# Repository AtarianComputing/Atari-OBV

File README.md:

# Atari-OBV
Project to create OpenBoardView files for the Atari line of computers to aid repair and restoration.

## OpenBoardView
Excellent open source board view software.
http://openboardview.org

## KiCad to BoardView Exporter
Python plugin to convert PCB file to OBV BRD.
https://github.com/whitequark/kicad-boardview

## Issues
My resulting BRD is mirrored and upside down for some reason. Haven't figured out how to fix it. But rotation and mirroring is quick and easy to do in software

Active low signals. KiCad needs to have the Pin/Net name enclosed in the tilde ~ character for it to display properly in KiCad. Those nets appear as ~BR~ in OBV. Easy enough to RegEx into /BR.

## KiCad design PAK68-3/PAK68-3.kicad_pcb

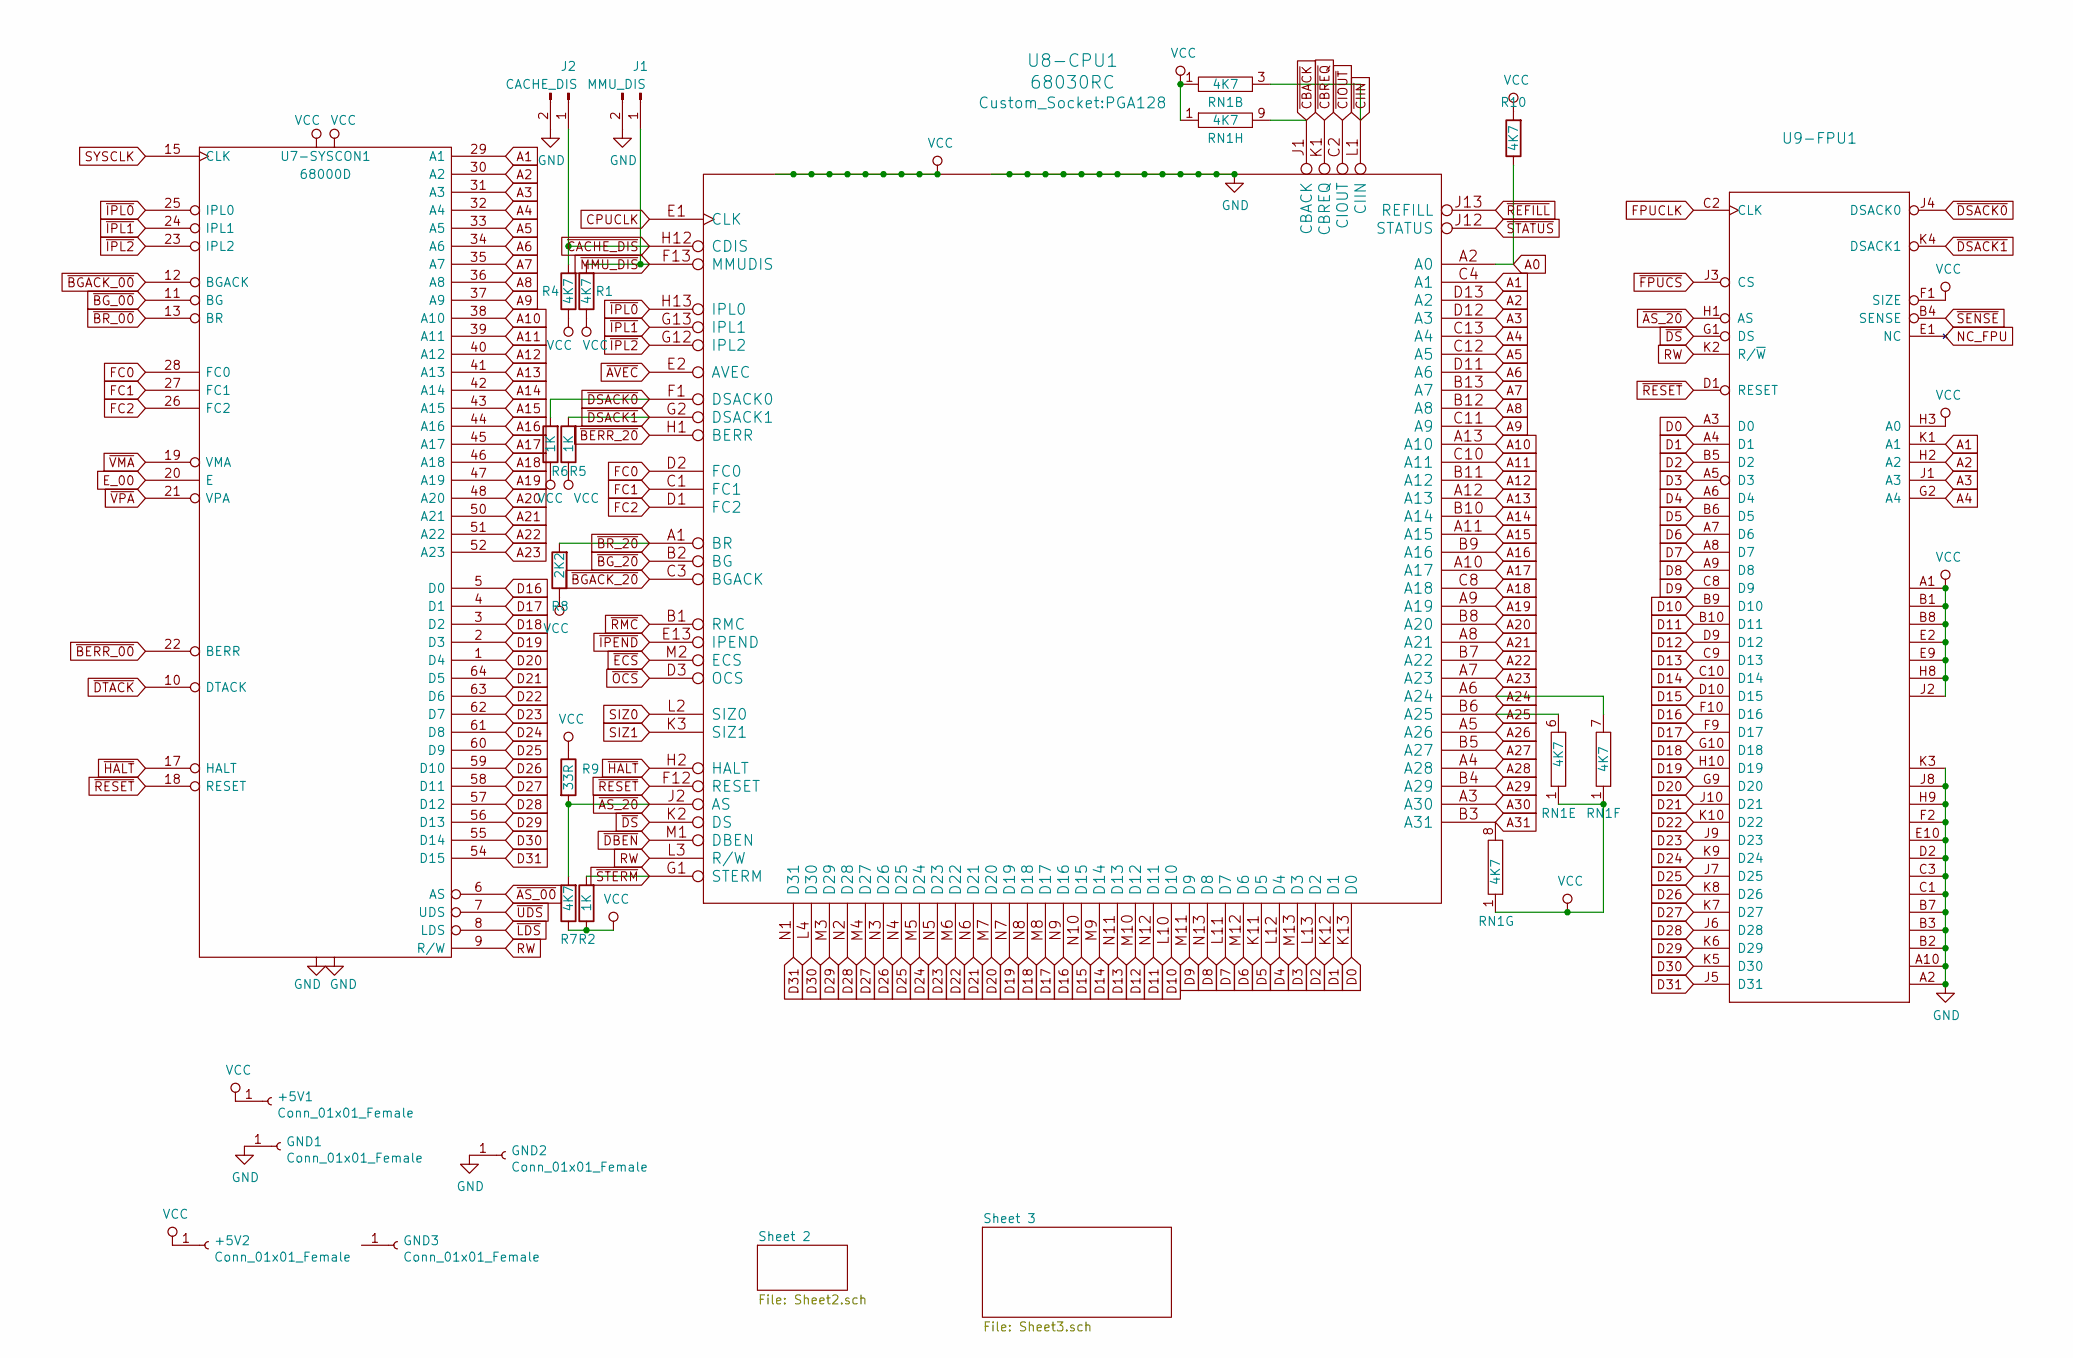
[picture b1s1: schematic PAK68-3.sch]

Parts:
+5V1, +5V2: Conn_01x01_Female; MountingHole_2.2mm_M2_DIN965_Pad
GND1, GND2, GND3: Conn_01x01_Female; MountingHole_2.2mm_M2_DIN965_Pad
J1: MMU_DIS; Socket_Strip_Straight_1x02_Pitch2.54mm
J2: CACHE_DIS; Socket_Strip_Straight_1x02_Pitch2.54mm
R1, R4, R7, R10: 4K7; R_Axial_DIN0207_L6.3mm_D2.5mm_P10.16mm_Horizontal
R2, R5, R6: 1K; R_Axial_DIN0207_L6.3mm_D2.5mm_P10.16mm_Horizontal
R8: 2K2; R_Axial_DIN0207_L6.3mm_D2.5mm_P10.16mm_Horizontal
R9: 33R; R_Axial_DIN0207_L6.3mm_D2.5mm_P10.16mm_Horizontal
RN1: 4K7; R_Array_SIP9
U7-SYSCON1: 68000D; DIP-64_W22.86mm_Socket
U8-CPU1: 68030RC; PGA128
U9-FPU1: MC68882; PGA68

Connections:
A0: R10.1, U8-CPU1.A2 (A0); also elsewhere on the board
A1: U7-SYSCON1.29 (A1), U8-CPU1.C4 (A1), U9-FPU1.K1 (A1); also elsewhere on the board
A2: U7-SYSCON1.30 (A2), U8-CPU1.D13 (A2), U9-FPU1.H2 (A2); also elsewhere on the board
A3: U7-SYSCON1.31 (A3), U8-CPU1.D12 (A3), U9-FPU1.J1 (A3); also elsewhere on the board
A4: U7-SYSCON1.32 (A4), U8-CPU1.C13 (A4), U9-FPU1.G2 (A4); also elsewhere on the board
A5: U7-SYSCON1.33 (A5), U8-CPU1.C12 (A5); also elsewhere on the board
A6: U7-SYSCON1.34 (A6), U8-CPU1.D11 (A6); also elsewhere on the board
A7: U7-SYSCON1.35 (A7), U8-CPU1.B13 (A7); also elsewhere on the board
A8: U7-SYSCON1.36 (A8), U8-CPU1.B12 (A8); also elsewhere on the board
A9: U7-SYSCON1.37 (A9), U8-CPU1.C11 (A9); also elsewhere on the board
A10: U7-SYSCON1.38 (A10), U8-CPU1.A13 (A10); also elsewhere on the board
A11: U7-SYSCON1.39 (A11), U8-CPU1.C10 (A11); also elsewhere on the board
A12: U7-SYSCON1.40 (A12), U8-CPU1.B11 (A12); also elsewhere on the board
A13: U7-SYSCON1.41 (A13), U8-CPU1.A12 (A13); also elsewhere on the board
A14: U7-SYSCON1.42 (A14), U8-CPU1.B10 (A14); also elsewhere on the board
A15: U7-SYSCON1.43 (A15), U8-CPU1.A11 (A15); also elsewhere on the board
A16: U7-SYSCON1.44 (A16), U8-CPU1.B9 (A16); also elsewhere on the board
A17: U7-SYSCON1.45 (A17), U8-CPU1.A10 (A17); also elsewhere on the board
A18: U7-SYSCON1.46 (A18), U8-CPU1.C8 (A18); also elsewhere on the board
A19: U7-SYSCON1.47 (A19), U8-CPU1.A9 (A19); also elsewhere on the board
A20: U7-SYSCON1.48 (A20), U8-CPU1.B8 (A20); also elsewhere on the board
A21: U7-SYSCON1.50 (A21), U8-CPU1.A8 (A21); also elsewhere on the board
A22: U7-SYSCON1.51 (A22), U8-CPU1.B7 (A22); also elsewhere on the board
A23: U7-SYSCON1.52 (A23), U8-CPU1.A7 (A23); also elsewhere on the board
A24: RN1.7, U8-CPU1.A6 (A24); also elsewhere on the board
A25: RN1.6, U8-CPU1.B6 (A25); also elsewhere on the board
A26: U8-CPU1.A5 (A26)
A27: U8-CPU1.B5 (A27)
A28: U8-CPU1.A4 (A28)
A29: U8-CPU1.B4 (A29)
A30: U8-CPU1.A3 (A30)
A31: RN1.8, U8-CPU1.B3 (A31); also elsewhere on the board
CPUCLK: U8-CPU1.E1 (CLK); also elsewhere on the board
D0: U8-CPU1.K13 (D0), U9-FPU1.A3 (D0); also elsewhere on the board
D1: U8-CPU1.K12 (D1), U9-FPU1.A4 (D1); also elsewhere on the board
D2: U8-CPU1.L13 (D2), U9-FPU1.B5 (D2); also elsewhere on the board
D3: U8-CPU1.M13 (D3), U9-FPU1.A5 (D3); also elsewhere on the board
D4: U8-CPU1.L12 (D4), U9-FPU1.A6 (D4); also elsewhere on the board
D5: U8-CPU1.K11 (D5), U9-FPU1.B6 (D5); also elsewhere on the board
D6: U8-CPU1.M12 (D6), U9-FPU1.A7 (D6); also elsewhere on the board
D7: U8-CPU1.L11 (D7), U9-FPU1.A8 (D7); also elsewhere on the board
D8: U8-CPU1.N13 (D8), U9-FPU1.A9 (D8); also elsewhere on the board
D9: U8-CPU1.M11 (D9), U9-FPU1.C8 (D9); also elsewhere on the board
D10: U8-CPU1.L10 (D10), U9-FPU1.B9 (D10); also elsewhere on the board
D11: U8-CPU1.N12 (D11), U9-FPU1.B10 (D11); also elsewhere on the board
D12: U8-CPU1.M10 (D12), U9-FPU1.D9 (D12); also elsewhere on the board
D13: U8-CPU1.N11 (D13), U9-FPU1.C9 (D13); also elsewhere on the board
D14: U8-CPU1.M9 (D14), U9-FPU1.C10 (D14); also elsewhere on the board
D15: U8-CPU1.N10 (D15), U9-FPU1.D10 (D15); also elsewhere on the board
D16: U7-SYSCON1.5 (D0), U8-CPU1.N9 (D16), U9-FPU1.F10 (D16); also elsewhere on the board
D17: U7-SYSCON1.4 (D1), U8-CPU1.M8 (D17), U9-FPU1.F9 (D17); also elsewhere on the board
D18: U7-SYSCON1.3 (D2), U8-CPU1.N8 (D18), U9-FPU1.G10 (D18); also elsewhere on the board
D19: U7-SYSCON1.2 (D3), U8-CPU1.N7 (D19), U9-FPU1.H10 (D19); also elsewhere on the board
D20: U7-SYSCON1.1 (D4), U8-CPU1.M7 (D20), U9-FPU1.G9 (D20); also elsewhere on the board
D21: U7-SYSCON1.64 (D5), U8-CPU1.N6 (D21), U9-FPU1.J10 (D21); also elsewhere on the board
D22: U7-SYSCON1.63 (D6), U8-CPU1.M6 (D22), U9-FPU1.K10 (D22); also elsewhere on the board
D23: U7-SYSCON1.62 (D7), U8-CPU1.N5 (D23), U9-FPU1.J9 (D23); also elsewhere on the board
D24: U7-SYSCON1.61 (D8), U8-CPU1.M5 (D24), U9-FPU1.K9 (D24); also elsewhere on the board
D25: U7-SYSCON1.60 (D9), U8-CPU1.N4 (D25), U9-FPU1.J7 (D25); also elsewhere on the board
D26: U7-SYSCON1.59 (D10), U8-CPU1.N3 (D26), U9-FPU1.K8 (D26); also elsewhere on the board
D27: U7-SYSCON1.58 (D11), U8-CPU1.M4 (D27), U9-FPU1.K7 (D27); also elsewhere on the board
D28: U7-SYSCON1.57 (D12), U8-CPU1.N2 (D28), U9-FPU1.J6 (D28); also elsewhere on the board
D29: U7-SYSCON1.56 (D13), U8-CPU1.M3 (D29), U9-FPU1.K6 (D29); also elsewhere on the board
D30: U7-SYSCON1.55 (D14), U8-CPU1.L4 (D30), U9-FPU1.K5 (D30); also elsewhere on the board
D31: U7-SYSCON1.54 (D15), U8-CPU1.N1 (D31), U9-FPU1.J5 (D31); also elsewhere on the board
E_00: U7-SYSCON1.20 (E); also elsewhere on the board
FC0: U7-SYSCON1.28 (FC0), U8-CPU1.D2 (FC0); also elsewhere on the board
FC1: U7-SYSCON1.27 (FC1), U8-CPU1.C1 (FC1); also elsewhere on the board
FC2: U7-SYSCON1.26 (FC2), U8-CPU1.D1 (FC2); also elsewhere on the board
FPUCLK: U9-FPU1.C2 (CLK); also elsewhere on the board
GND: GND1.1, GND2.1, J1.2, J2.2, U7-SYSCON1.16 (GND), U7-SYSCON1.53 (GND), U8-CPU1.C5 (GND), U8-CPU1.C7 (GND), U8-CPU1.C9 (GND), U8-CPU1.E3 (GND), U8-CPU1.E11 (GND), U8-CPU1.F3 (GND), U8-CPU1.G3 (GND), U8-CPU1.G11 (GND), U8-CPU1.J3 (GND), U8-CPU1.J11 (GND), U8-CPU1.L5 (GND), U8-CPU1.L7 (GND), U8-CPU1.L8 (GND), U8-CPU1.L9 (GND), U9-FPU1.A2 (GND@1), U9-FPU1.A10 (GND@2), U9-FPU1.B2 (GND@3), U9-FPU1.B3 (GND@4), U9-FPU1.B7 (GND@5), U9-FPU1.C1 (GND@6), U9-FPU1.C3 (GND@7), U9-FPU1.D2 (GND@8), U9-FPU1.E10 (GND@9), U9-FPU1.F2 (GND@10), U9-FPU1.H9 (GND@11), U9-FPU1.J8 (GND@12), U9-FPU1.K3 (GND@13); also elsewhere on the board
NC_FPU: U9-FPU1.E1 (NC)
RW: U7-SYSCON1.9 (R/W), U8-CPU1.L3 (R/W), U9-FPU1.K2 (R/~W); also elsewhere on the board
SIZ0: U8-CPU1.L2 (SIZ0); also elsewhere on the board
SIZ1: U8-CPU1.K3 (SIZ1); also elsewhere on the board
SYSCLK: U7-SYSCON1.15 (CLK); also elsewhere on the board
VCC: +5V1.1, +5V2.1, R1.1, R2.1, R4.1, R5.1, R6.1, R7.1, R8.1, R9.1, R10.2, RN1.1, U7-SYSCON1.14 (VCC), U7-SYSCON1.49 (VCC), U8-CPU1.C6 (VCC), U8-CPU1.D4 (VCC), U8-CPU1.D10 (VCC), U8-CPU1.F2 (VCC), U8-CPU1.F11 (VCC), U8-CPU1.H3 (VCC), U8-CPU1.H11 (VCC), U8-CPU1.K4 (VCC), U8-CPU1.K10 (VCC), U8-CPU1.L6 (VCC), U9-FPU1.A1 (VCC@1), U9-FPU1.B1 (VCC@2), U9-FPU1.B8 (VCC@3), U9-FPU1.E2 (VCC@4), U9-FPU1.E9 (VCC@5), U9-FPU1.F1 (SIZE), U9-FPU1.H3 (A0), U9-FPU1.H8 (VCC@6), U9-FPU1.J2 (VCC@7); also elsewhere on the board
~AS_00~: U7-SYSCON1.6 (AS); also elsewhere on the board
~AS_20~: R7.2, R9.2, U8-CPU1.J2 (AS), U9-FPU1.H1 (AS); also elsewhere on the board
~AVEC~: U8-CPU1.E2 (AVEC); also elsewhere on the board
~BERR_00~: U7-SYSCON1.22 (BERR); also elsewhere on the board
~BERR_20~: U8-CPU1.H1 (BERR); also elsewhere on the board
~BGACK_00~: U7-SYSCON1.12 (BGACK); also elsewhere on the board
~BGACK_20~: U8-CPU1.C3 (BGACK); also elsewhere on the board
~BG_00~: U7-SYSCON1.11 (BG); also elsewhere on the board
~BG_20~: U8-CPU1.B2 (BG); also elsewhere on the board
~BR_00~: U7-SYSCON1.13 (BR); also elsewhere on the board
~BR_20~: R8.2, U8-CPU1.A1 (BR); also elsewhere on the board
~CACHE_DIS~: J2.1, R4.2, U8-CPU1.H12 (CDIS)
~CBACK~: RN1.9, U8-CPU1.J1 (CBACK)
~CBREQ~: U8-CPU1.K1 (CBREQ)
~CIIN~: RN1.3, U8-CPU1.L1 (CIIN)
~CIOUT~: U8-CPU1.C2 (CIOUT)
~DBEN~: U8-CPU1.M1 (DBEN)
~DSACK0~: R6.2, U8-CPU1.F1 (DSACK0), U9-FPU1.J4 (DSACK0); also elsewhere on the board
~DSACK1~: R5.2, U8-CPU1.G2 (DSACK1), U9-FPU1.K4 (DSACK1); also elsewhere on the board
~DS~: U8-CPU1.K2 (DS), U9-FPU1.G1 (DS); also elsewhere on the board
~DTACK~: U7-SYSCON1.10 (DTACK); also elsewhere on the board
~ECS~: U8-CPU1.M2 (ECS)
~FPUCS~: U9-FPU1.J3 (CS); also elsewhere on the board
~HALT~: U7-SYSCON1.17 (HALT), U8-CPU1.H2 (HALT); also elsewhere on the board
~IPEND~: U8-CPU1.E13 (IPEND)
~IPL0~: U7-SYSCON1.25 (IPL0), U8-CPU1.H13 (IPL0); also elsewhere on the board
~IPL1~: U7-SYSCON1.24 (IPL1), U8-CPU1.G13 (IPL1); also elsewhere on the board
~IPL2~: U7-SYSCON1.23 (IPL2), U8-CPU1.G12 (IPL2); also elsewhere on the board
~LDS~: U7-SYSCON1.8 (LDS); also elsewhere on the board
~MMU_DIS~: J1.1, R1.2, U8-CPU1.F13 (MMUDIS)
~OCS~: U8-CPU1.D3 (OCS)
~REFILL~: U8-CPU1.J13 (REFILL)
~RESET~: U7-SYSCON1.18 (RESET), U8-CPU1.F12 (RESET), U9-FPU1.D1 (RESET); also elsewhere on the board
~RMC~: U8-CPU1.B1 (RMC)
~SENSE~: U9-FPU1.B4 (SENSE)
~STATUS~: U8-CPU1.J12 (STATUS)
~STERM~: R2.2, U8-CPU1.G1 (STERM)
~UDS~: U7-SYSCON1.7 (UDS); also elsewhere on the board
~VMA~: U7-SYSCON1.19 (VMA); also elsewhere on the board
~VPA~: U7-SYSCON1.21 (VPA); also elsewhere on the board

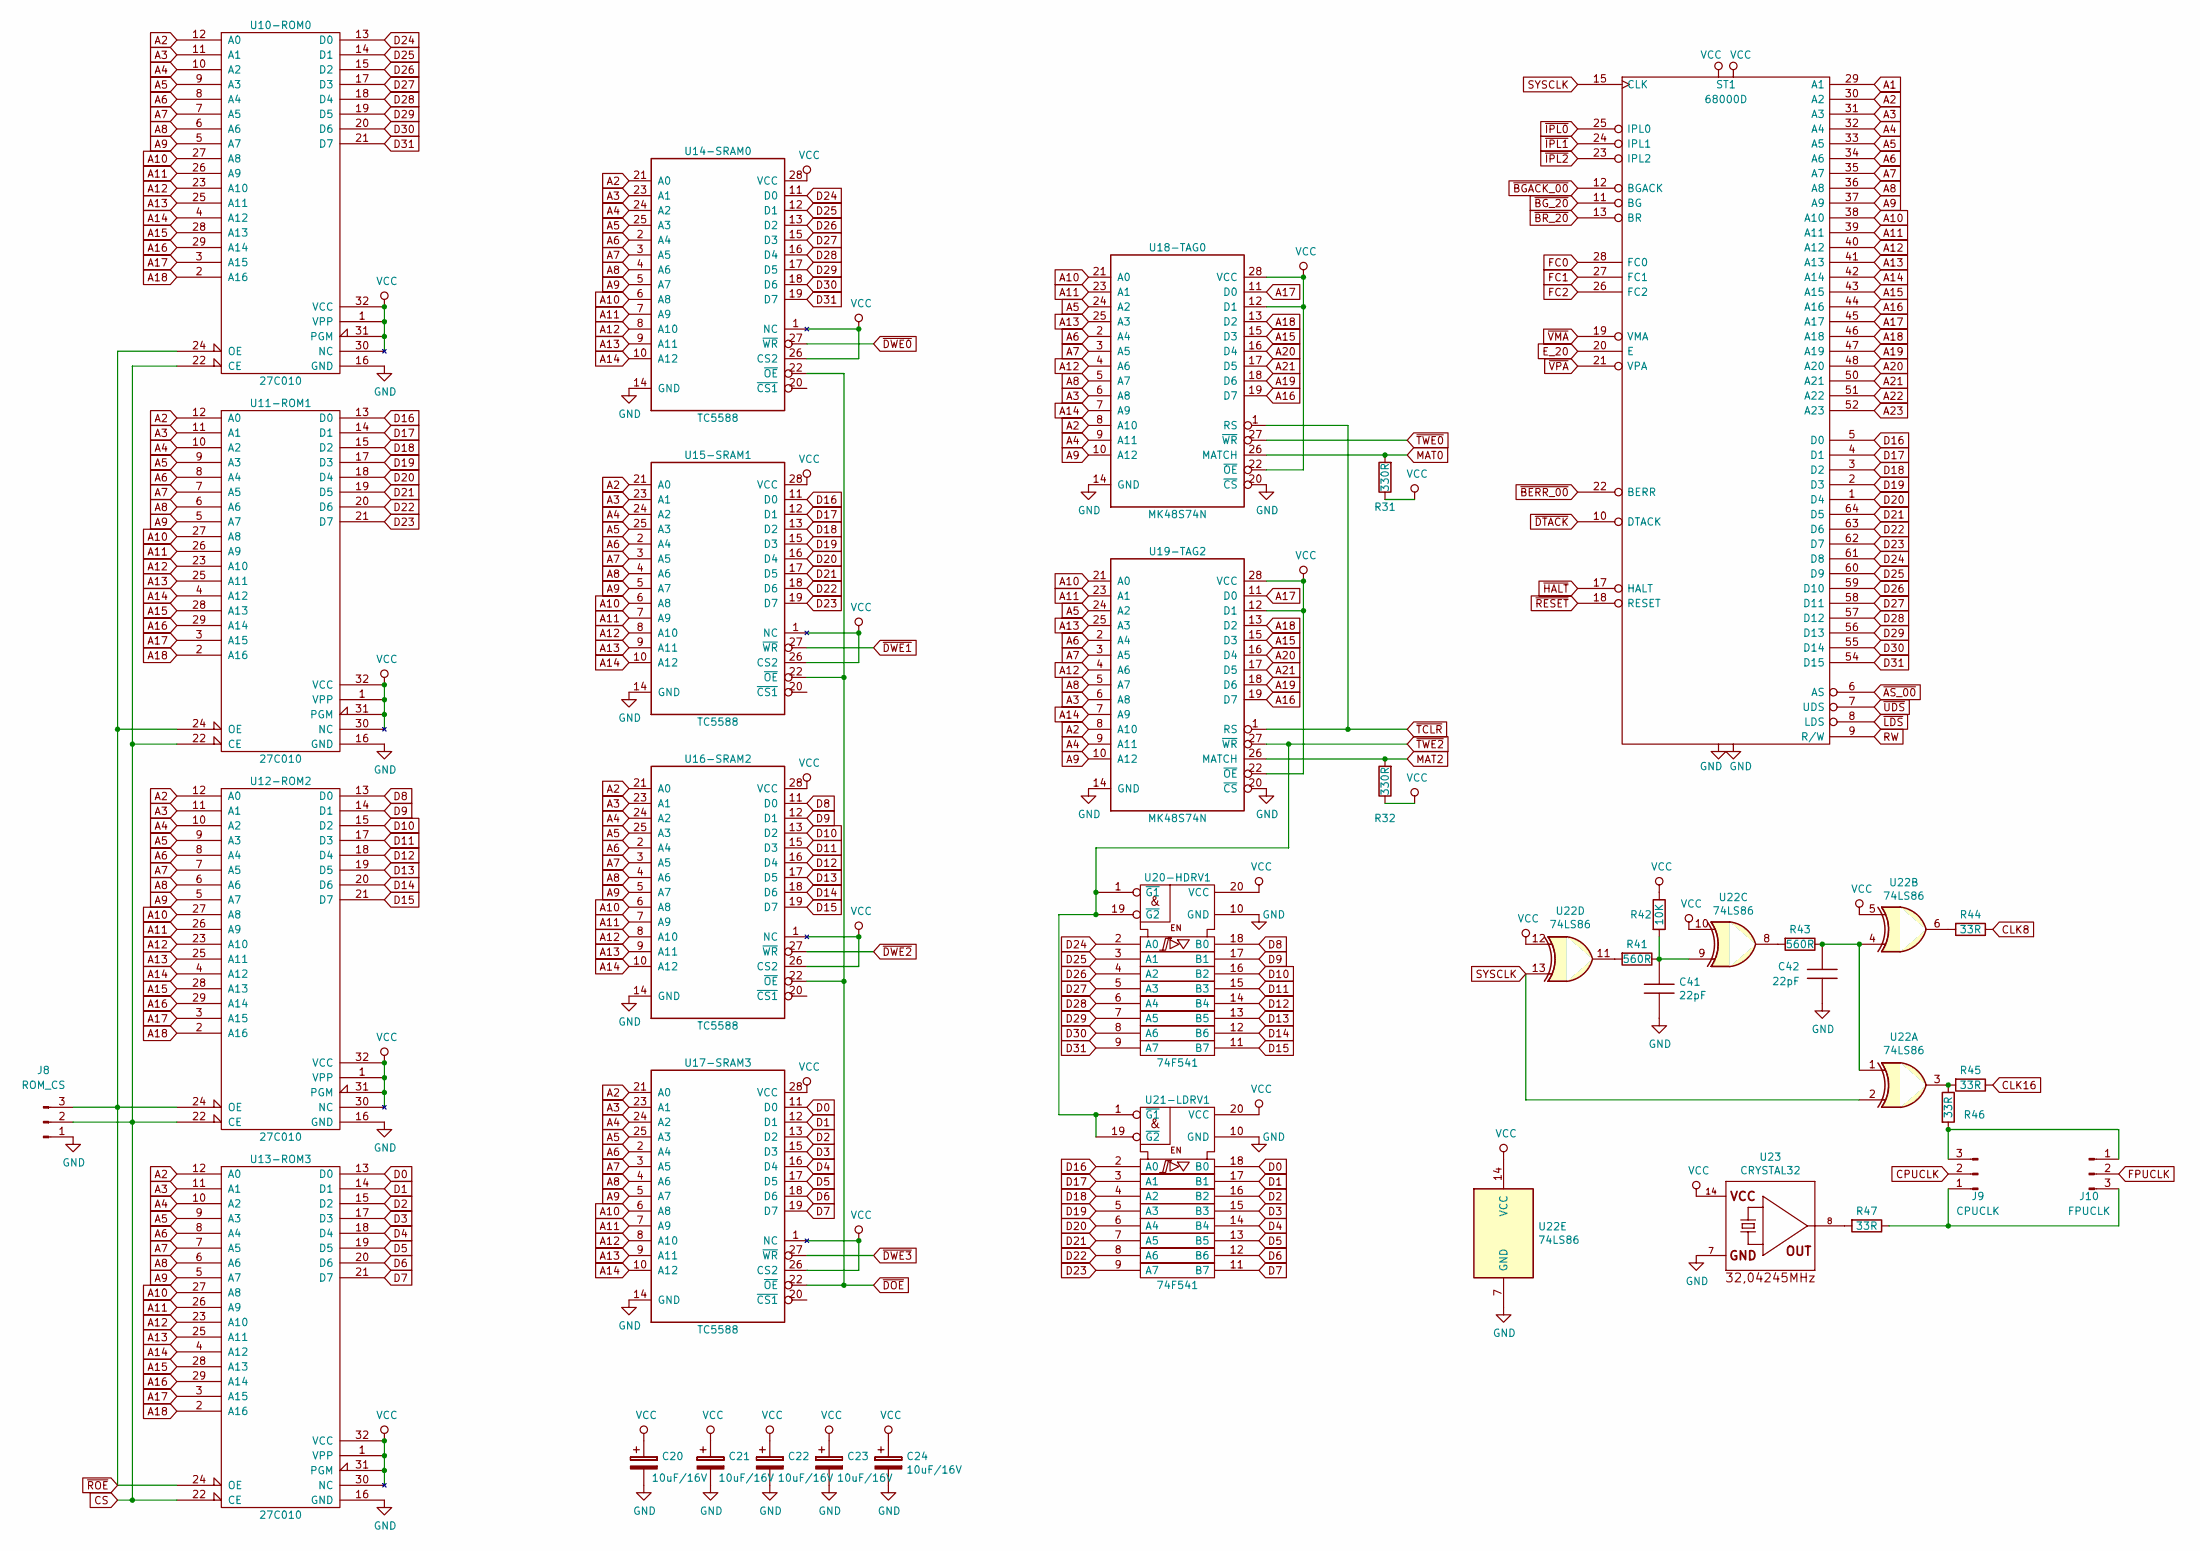
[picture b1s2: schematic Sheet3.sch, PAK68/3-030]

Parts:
C20, C21, C22, C23, C24: 10uF/16V; CP_Radial_Tantal_D4.5mm_P2.50mm
C41, C42: 22pF; C_Rect_L4.0mm_W2.5mm_P2.50mm
J8: ROM_CS; Socket_Strip_Straight_1x03_Pitch2.54mm
J9: CPUCLK; Socket_Strip_Straight_1x03_Pitch2.54mm
J10: FPUCLK; Socket_Strip_Straight_1x03_Pitch2.54mm
R31, R32: 330R; R_Axial_DIN0207_L6.3mm_D2.5mm_P10.16mm_Horizontal
R41, R43: 560R; R_Axial_DIN0207_L6.3mm_D2.5mm_P10.16mm_Horizontal
R42: 10K; R_Axial_DIN0207_L6.3mm_D2.5mm_P10.16mm_Horizontal
R44, R45, R46, R47: 33R; R_Axial_DIN0207_L6.3mm_D2.5mm_P10.16mm_Horizontal
ST1: 68000D; DIP-64_W22.86mm_Socket
U10-ROM0, U11-ROM1, U12-ROM2, U13-ROM3: 27C010; DIP-32_W15.24mm
U14-SRAM0, U15-SRAM1, U16-SRAM2, U17-SRAM3: TC5588; DIP-28_W7.62mm
U18-TAG0, U19-TAG2: MK48S74N; DIP-28_W7.62mm
U20-HDRV1, U21-LDRV1: 74F541; DIP-20_W7.62mm
U22: 74LS86; DIP-14_W7.62mm
U23: CRYSTAL32; Oscillator_DIP-14

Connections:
A1: ST1.29 (A1); also elsewhere on the board
A2: ST1.30 (A2), U10-ROM0.12 (A0), U11-ROM1.12 (A0), U12-ROM2.12 (A0), U13-ROM3.12 (A0), U14-SRAM0.21 (A0), U15-SRAM1.21 (A0), U16-SRAM2.21 (A0), U17-SRAM3.21 (A0), U18-TAG0.8 (A10), U19-TAG2.8 (A10); also elsewhere on the board
A3: ST1.31 (A3), U10-ROM0.11 (A1), U11-ROM1.11 (A1), U12-ROM2.11 (A1), U13-ROM3.11 (A1), U14-SRAM0.23 (A1), U15-SRAM1.23 (A1), U16-SRAM2.23 (A1), U17-SRAM3.23 (A1), U18-TAG0.6 (A8), U19-TAG2.6 (A8); also elsewhere on the board
A4: ST1.32 (A4), U10-ROM0.10 (A2), U11-ROM1.10 (A2), U12-ROM2.10 (A2), U13-ROM3.10 (A2), U14-SRAM0.24 (A2), U15-SRAM1.24 (A2), U16-SRAM2.24 (A2), U17-SRAM3.24 (A2), U18-TAG0.9 (A11), U19-TAG2.9 (A11); also elsewhere on the board
A5: ST1.33 (A5), U10-ROM0.9 (A3), U11-ROM1.9 (A3), U12-ROM2.9 (A3), U13-ROM3.9 (A3), U14-SRAM0.25 (A3), U15-SRAM1.25 (A3), U16-SRAM2.25 (A3), U17-SRAM3.25 (A3), U18-TAG0.24 (A2), U19-TAG2.24 (A2); also elsewhere on the board
A6: ST1.34 (A6), U10-ROM0.8 (A4), U11-ROM1.8 (A4), U12-ROM2.8 (A4), U13-ROM3.8 (A4), U14-SRAM0.2 (A4), U15-SRAM1.2 (A4), U16-SRAM2.2 (A4), U17-SRAM3.2 (A4), U18-TAG0.2 (A4), U19-TAG2.2 (A4); also elsewhere on the board
A7: ST1.35 (A7), U10-ROM0.7 (A5), U11-ROM1.7 (A5), U12-ROM2.7 (A5), U13-ROM3.7 (A5), U14-SRAM0.3 (A5), U15-SRAM1.3 (A5), U16-SRAM2.3 (A5), U17-SRAM3.3 (A5), U18-TAG0.3 (A5), U19-TAG2.3 (A5); also elsewhere on the board
A8: ST1.36 (A8), U10-ROM0.6 (A6), U11-ROM1.6 (A6), U12-ROM2.6 (A6), U13-ROM3.6 (A6), U14-SRAM0.4 (A6), U15-SRAM1.4 (A6), U16-SRAM2.4 (A6), U17-SRAM3.4 (A6), U18-TAG0.5 (A7), U19-TAG2.5 (A7); also elsewhere on the board
A9: ST1.37 (A9), U10-ROM0.5 (A7), U11-ROM1.5 (A7), U12-ROM2.5 (A7), U13-ROM3.5 (A7), U14-SRAM0.5 (A7), U15-SRAM1.5 (A7), U16-SRAM2.5 (A7), U17-SRAM3.5 (A7), U18-TAG0.10 (A12), U19-TAG2.10 (A12); also elsewhere on the board
A10: ST1.38 (A10), U10-ROM0.27 (A8), U11-ROM1.27 (A8), U12-ROM2.27 (A8), U13-ROM3.27 (A8), U14-SRAM0.6 (A8), U15-SRAM1.6 (A8), U16-SRAM2.6 (A8), U17-SRAM3.6 (A8), U18-TAG0.21 (A0), U19-TAG2.21 (A0); also elsewhere on the board
A11: ST1.39 (A11), U10-ROM0.26 (A9), U11-ROM1.26 (A9), U12-ROM2.26 (A9), U13-ROM3.26 (A9), U14-SRAM0.7 (A9), U15-SRAM1.7 (A9), U16-SRAM2.7 (A9), U17-SRAM3.7 (A9), U18-TAG0.23 (A1), U19-TAG2.23 (A1); also elsewhere on the board
A12: ST1.40 (A12), U10-ROM0.23 (A10), U11-ROM1.23 (A10), U12-ROM2.23 (A10), U13-ROM3.23 (A10), U14-SRAM0.8 (A10), U15-SRAM1.8 (A10), U16-SRAM2.8 (A10), U17-SRAM3.8 (A10), U18-TAG0.4 (A6), U19-TAG2.4 (A6); also elsewhere on the board
A13: ST1.41 (A13), U10-ROM0.25 (A11), U11-ROM1.25 (A11), U12-ROM2.25 (A11), U13-ROM3.25 (A11), U14-SRAM0.9 (A11), U15-SRAM1.9 (A11), U16-SRAM2.9 (A11), U17-SRAM3.9 (A11), U18-TAG0.25 (A3), U19-TAG2.25 (A3); also elsewhere on the board
A14: ST1.42 (A14), U10-ROM0.4 (A12), U11-ROM1.4 (A12), U12-ROM2.4 (A12), U13-ROM3.4 (A12), U14-SRAM0.10 (A12), U15-SRAM1.10 (A12), U16-SRAM2.10 (A12), U17-SRAM3.10 (A12), U18-TAG0.7 (A9), U19-TAG2.7 (A9); also elsewhere on the board
A15: ST1.43 (A15), U10-ROM0.28 (A13), U11-ROM1.28 (A13), U12-ROM2.28 (A13), U13-ROM3.28 (A13), U18-TAG0.15 (D3), U19-TAG2.15 (D3); also elsewhere on the board
A16: ST1.44 (A16), U10-ROM0.29 (A14), U11-ROM1.29 (A14), U12-ROM2.29 (A14), U13-ROM3.29 (A14), U18-TAG0.19 (D7), U19-TAG2.19 (D7); also elsewhere on the board
A17: ST1.45 (A17), U10-ROM0.3 (A15), U11-ROM1.3 (A15), U12-ROM2.3 (A15), U13-ROM3.3 (A15), U18-TAG0.11 (D0), U19-TAG2.11 (D0); also elsewhere on the board
A18: ST1.46 (A18), U10-ROM0.2 (A16), U11-ROM1.2 (A16), U12-ROM2.2 (A16), U13-ROM3.2 (A16), U18-TAG0.13 (D2), U19-TAG2.13 (D2); also elsewhere on the board
A19: ST1.47 (A19), U18-TAG0.18 (D6), U19-TAG2.18 (D6); also elsewhere on the board
A20: ST1.48 (A20), U18-TAG0.16 (D4), U19-TAG2.16 (D4); also elsewhere on the board
A21: ST1.50 (A21), U18-TAG0.17 (D5), U19-TAG2.17 (D5); also elsewhere on the board
A22: ST1.51 (A22); also elsewhere on the board
A23: ST1.52 (A23); also elsewhere on the board
CLK8: R44.1; also elsewhere on the board
CLK16: R45.1; also elsewhere on the board
CPUCLK: J9.2; also elsewhere on the board
CS: J8.2, U10-ROM0.22 (CE), U11-ROM1.22 (CE), U12-ROM2.22 (CE), U13-ROM3.22 (CE)
D0: U13-ROM3.13 (D0), U17-SRAM3.11 (D0), U21-LDRV1.18 (B0); also elsewhere on the board
D1: U13-ROM3.14 (D1), U17-SRAM3.12 (D1), U21-LDRV1.17 (B1); also elsewhere on the board
D2: U13-ROM3.15 (D2), U17-SRAM3.13 (D2), U21-LDRV1.16 (B2); also elsewhere on the board
D3: U13-ROM3.17 (D3), U17-SRAM3.15 (D3), U21-LDRV1.15 (B3); also elsewhere on the board
D4: U13-ROM3.18 (D4), U17-SRAM3.16 (D4), U21-LDRV1.14 (B4); also elsewhere on the board
D5: U13-ROM3.19 (D5), U17-SRAM3.17 (D5), U21-LDRV1.13 (B5); also elsewhere on the board
D6: U13-ROM3.20 (D6), U17-SRAM3.18 (D6), U21-LDRV1.12 (B6); also elsewhere on the board
D7: U13-ROM3.21 (D7), U17-SRAM3.19 (D7), U21-LDRV1.11 (B7); also elsewhere on the board
D8: U12-ROM2.13 (D0), U16-SRAM2.11 (D0), U20-HDRV1.18 (B0); also elsewhere on the board
D9: U12-ROM2.14 (D1), U16-SRAM2.12 (D1), U20-HDRV1.17 (B1); also elsewhere on the board
D10: U12-ROM2.15 (D2), U16-SRAM2.13 (D2), U20-HDRV1.16 (B2); also elsewhere on the board
D11: U12-ROM2.17 (D3), U16-SRAM2.15 (D3), U20-HDRV1.15 (B3); also elsewhere on the board
D12: U12-ROM2.18 (D4), U16-SRAM2.16 (D4), U20-HDRV1.14 (B4); also elsewhere on the board
D13: U12-ROM2.19 (D5), U16-SRAM2.17 (D5), U20-HDRV1.13 (B5); also elsewhere on the board
D14: U12-ROM2.20 (D6), U16-SRAM2.18 (D6), U20-HDRV1.12 (B6); also elsewhere on the board
D15: U12-ROM2.21 (D7), U16-SRAM2.19 (D7), U20-HDRV1.11 (B7); also elsewhere on the board
D16: ST1.5 (D0), U11-ROM1.13 (D0), U15-SRAM1.11 (D0), U21-LDRV1.2 (A0); also elsewhere on the board
D17: ST1.4 (D1), U11-ROM1.14 (D1), U15-SRAM1.12 (D1), U21-LDRV1.3 (A1); also elsewhere on the board
D18: ST1.3 (D2), U11-ROM1.15 (D2), U15-SRAM1.13 (D2), U21-LDRV1.4 (A2); also elsewhere on the board
D19: ST1.2 (D3), U11-ROM1.17 (D3), U15-SRAM1.15 (D3), U21-LDRV1.5 (A3); also elsewhere on the board
D20: ST1.1 (D4), U11-ROM1.18 (D4), U15-SRAM1.16 (D4), U21-LDRV1.6 (A4); also elsewhere on the board
D21: ST1.64 (D5), U11-ROM1.19 (D5), U15-SRAM1.17 (D5), U21-LDRV1.7 (A5); also elsewhere on the board
D22: ST1.63 (D6), U11-ROM1.20 (D6), U15-SRAM1.18 (D6), U21-LDRV1.8 (A6); also elsewhere on the board
D23: ST1.62 (D7), U11-ROM1.21 (D7), U15-SRAM1.19 (D7), U21-LDRV1.9 (A7); also elsewhere on the board
D24: ST1.61 (D8), U10-ROM0.13 (D0), U14-SRAM0.11 (D0), U20-HDRV1.2 (A0); also elsewhere on the board
D25: ST1.60 (D9), U10-ROM0.14 (D1), U14-SRAM0.12 (D1), U20-HDRV1.3 (A1); also elsewhere on the board
D26: ST1.59 (D10), U10-ROM0.15 (D2), U14-SRAM0.13 (D2), U20-HDRV1.4 (A2); also elsewhere on the board
D27: ST1.58 (D11), U10-ROM0.17 (D3), U14-SRAM0.15 (D3), U20-HDRV1.5 (A3); also elsewhere on the board
D28: ST1.57 (D12), U10-ROM0.18 (D4), U14-SRAM0.16 (D4), U20-HDRV1.6 (A4); also elsewhere on the board
D29: ST1.56 (D13), U10-ROM0.19 (D5), U14-SRAM0.17 (D5), U20-HDRV1.7 (A5); also elsewhere on the board
D30: ST1.55 (D14), U10-ROM0.20 (D6), U14-SRAM0.18 (D6), U20-HDRV1.8 (A6); also elsewhere on the board
D31: ST1.54 (D15), U10-ROM0.21 (D7), U14-SRAM0.19 (D7), U20-HDRV1.9 (A7); also elsewhere on the board
E_20: ST1.20 (E); also elsewhere on the board
FC0: ST1.28 (FC0); also elsewhere on the board
FC1: ST1.27 (FC1); also elsewhere on the board
FC2: ST1.26 (FC2); also elsewhere on the board
FPUCLK: J10.2; also elsewhere on the board
GND: C20.2, C21.2, C22.2, C23.2, C24.2, C41.2, C42.2, J8.1, ST1.16 (GND), ST1.53 (GND), U10-ROM0.16 (GND), U11-ROM1.16 (GND), U12-ROM2.16 (GND), U13-ROM3.16 (GND), U14-SRAM0.14 (GND), U15-SRAM1.14 (GND), U16-SRAM2.14 (GND), U17-SRAM3.14 (GND), U18-TAG0.14 (GND), U18-TAG0.20 (~CS~), U19-TAG2.14 (GND), U19-TAG2.20 (~CS~), U20-HDRV1.10 (GND), U21-LDRV1.10 (GND), U22.7 (GND), U23.7; also elsewhere on the board
MAT0: R31.2, U18-TAG0.26 (MATCH); also elsewhere on the board
MAT2: R32.2, U19-TAG2.26 (MATCH); also elsewhere on the board
unnamed: C41.1, R41.1, R42.2, U22.9
unnamed: C42.1, R43.1, U22.1, U22.4
unnamed: J9.3, J10.1, R46.2
unnamed: J9.1, J10.3, R47.1
unnamed: R41.2, U22.11
unnamed: R43.2, U22.8
unnamed: R44.2, U22.6
unnamed: R45.2, R46.1, U22.3
unnamed: R47.2, U23.8
RW: ST1.9 (R/W); also elsewhere on the board
SYSCLK: ST1.15 (CLK), U22.2, U22.13; also elsewhere on the board
VCC: C20.1, C21.1, C22.1, C23.1, C24.1, R31.1, R32.1, R42.1, ST1.14 (VCC), ST1.49 (VCC), U10-ROM0.1 (VPP), U10-ROM0.30 (NC), U10-ROM0.31 (PGM), U10-ROM0.32 (VCC), U11-ROM1.1 (VPP), U11-ROM1.30 (NC), U11-ROM1.31 (PGM), U11-ROM1.32 (VCC), U12-ROM2.1 (VPP), U12-ROM2.30 (NC), U12-ROM2.31 (PGM), U12-ROM2.32 (VCC), U13-ROM3.1 (VPP), U13-ROM3.30 (NC), U13-ROM3.31 (PGM), U13-ROM3.32 (VCC), U14-SRAM0.1 (NC), U14-SRAM0.26 (CS2), U14-SRAM0.28 (VCC), U15-SRAM1.1 (NC), U15-SRAM1.26 (CS2), U15-SRAM1.28 (VCC), U16-SRAM2.1 (NC), U16-SRAM2.26 (CS2), U16-SRAM2.28 (VCC), U17-SRAM3.1 (NC), U17-SRAM3.26 (CS2), U17-SRAM3.28 (VCC), U18-TAG0.12 (D1), U18-TAG0.22 (~OE~), U18-TAG0.28 (VCC), U19-TAG2.12 (D1), U19-TAG2.22 (~OE~), U19-TAG2.28 (VCC), U20-HDRV1.20 (VCC), U21-LDRV1.20 (VCC), U22.5, U22.10, U22.12, U22.14 (VCC), U23.14; also elsewhere on the board
~AS_00~: ST1.6 (AS); also elsewhere on the board
~BERR_00~: ST1.22 (BERR); also elsewhere on the board
~BGACK_00~: ST1.12 (BGACK); also elsewhere on the board
~BG_20~: ST1.11 (BG); also elsewhere on the board
~BR_20~: ST1.13 (BR); also elsewhere on the board
~DOE~: U14-SRAM0.22 (~OE~), U15-SRAM1.22 (~OE~), U16-SRAM2.22 (~OE~), U17-SRAM3.22 (~OE~); also elsewhere on the board
~DTACK~: ST1.10 (DTACK); also elsewhere on the board
~DWE0~: U14-SRAM0.27 (~WR~); also elsewhere on the board
~DWE1~: U15-SRAM1.27 (~WR~); also elsewhere on the board
~DWE2~: U16-SRAM2.27 (~WR~); also elsewhere on the board
~DWE3~: U17-SRAM3.27 (~WR~); also elsewhere on the board
~HALT~: ST1.17 (HALT); also elsewhere on the board
~IPL0~: ST1.25 (IPL0); also elsewhere on the board
~IPL1~: ST1.24 (IPL1); also elsewhere on the board
~IPL2~: ST1.23 (IPL2); also elsewhere on the board
~LDS~: ST1.8 (LDS); also elsewhere on the board
~RESET~: ST1.18 (RESET); also elsewhere on the board
~ROE~: J8.3, U10-ROM0.24 (OE), U11-ROM1.24 (OE), U12-ROM2.24 (OE), U13-ROM3.24 (OE); also elsewhere on the board
~TCLR~: U18-TAG0.1 (RS), U19-TAG2.1 (RS); also elsewhere on the board
~TWE0~: U18-TAG0.27 (~WR~); also elsewhere on the board
~TWE2~: U19-TAG2.27 (~WR~), U20-HDRV1.1 (~G1), U20-HDRV1.19 (~G2), U21-LDRV1.1 (~G1), U21-LDRV1.19 (~G2); also elsewhere on the board
~UDS~: ST1.7 (UDS); also elsewhere on the board
~VMA~: ST1.19 (VMA); also elsewhere on the board
~VPA~: ST1.21 (VPA); also elsewhere on the board
